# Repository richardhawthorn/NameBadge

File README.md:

### Description

NameBadge SMD

### Features

- 20 LED display
- Charlieplex LED control
- ATTINY44 processor
- 3V operation @ 1Mhz or 8Mhz
- 1x button
- ICSP port

### License

This work is licensed under a Creative Commons Attribution-ShareAlike 4.0 International License.

<br />
Designed by <a xmlns:cc="http://creativecommons.org/ns#" href="http://www.richardhawthorn.com" property="cc:attributionName" rel="cc:attributionURL" target="_blank">Richard Hawthorn</a><br />
<a rel="license" href="http://creativecommons.org/licenses/by-sa/4.0/" target="_blank">View License</a>

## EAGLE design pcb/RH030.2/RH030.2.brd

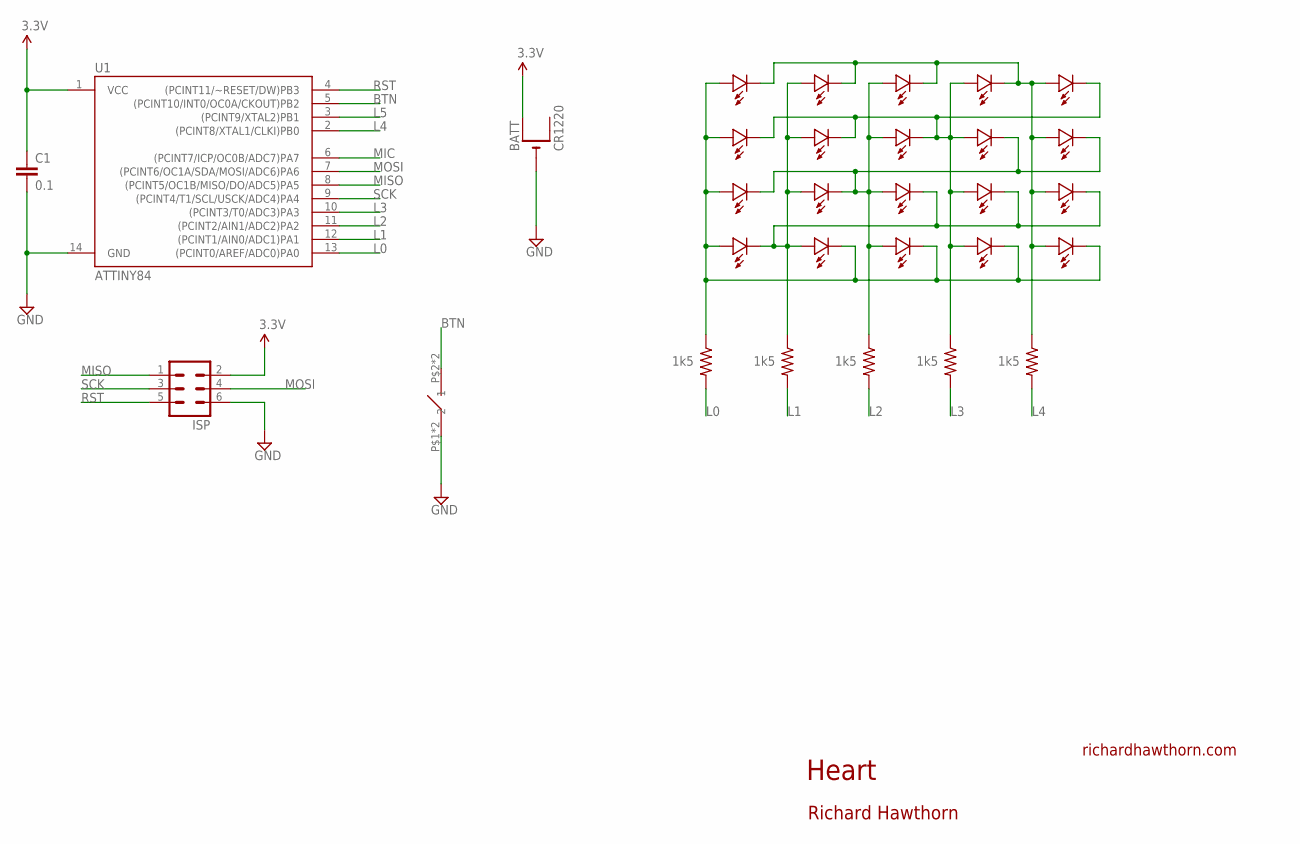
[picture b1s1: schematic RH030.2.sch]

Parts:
BATT: CR1220; CR1220-SMD
BTN1: TURTLE-3PIN
C1: 0.1; 0603-CAP
ISP: MA03-2
LED1, LED2, LED3, LED4, LED5, LED6, LED7, LED8, LED9, LED10, LED11, LED12, LED13, LED14, LED15, LED16, LED17, LED18, LED19, LED20: LED0603; 0603-LED
R1, R2, R3, R4, R5: 1k5; 0603-RES
U1: ATTINY84; SO14

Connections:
BTN: BTN1.P$2 (2), BTN1.P$4 (2), U1.5 ((PCINT10/INT0/OC0A/CKOUT)PB2)
GND: BATT.-, BTN1.P$1 (1), BTN1.P$3 (1), C1.2, ISP.6, U1.14 (GND)
L0: R1.2, U1.13 ((PCINT0/AREF/ADC0)PA0)
L1: R2.2, U1.12 ((PCINT1/AIN0/ADC1)PA1)
L2: R3.2, U1.11 ((PCINT2/AIN1/ADC2)PA2)
L3: R4.2, U1.10 ((PCINT3/T0/ADC3)PA3)
L4: R5.2, U1.2 ((PCINT8/XTAL1/CLKI)PB0)
L5: U1.3 ((PCINT9/XTAL2)PB1)
MIC: U1.6 ((PCINT7/ICP/OC0B/ADC7)PA7)
MISO: ISP.1, U1.8 ((PCINT5/OC1B/MISO/DO/ADC5)PA5)
MOSI: ISP.4, U1.7 ((PCINT6/OC1A/SDA/MOSI/ADC6)PA6)
unnamed: LED2.PLUS, LED7.PLUS, LED12.PLUS, LED13.MINUS, LED14.MINUS, LED15.MINUS, LED16.MINUS, LED17.PLUS, R2.1
unnamed: LED1.PLUS, LED6.PLUS, LED11.PLUS, LED16.PLUS, LED17.MINUS, LED18.MINUS, LED19.MINUS, LED20.MINUS, R1.1
unnamed: LED1.MINUS, LED2.MINUS, LED3.MINUS, LED4.MINUS, LED5.PLUS, LED10.PLUS, LED15.PLUS, LED20.PLUS, R5.1
unnamed: LED4.PLUS, LED5.MINUS, LED6.MINUS, LED7.MINUS, LED8.MINUS, LED9.PLUS, LED14.PLUS, LED19.PLUS, R4.1
unnamed: LED3.PLUS, LED8.PLUS, LED9.MINUS, LED10.MINUS, LED11.MINUS, LED12.MINUS, LED13.PLUS, LED18.PLUS, R3.1
RST: ISP.5, U1.4 ((PCINT11/~RESET/DW)PB3)
SCK: ISP.3, U1.9 ((PCINT4/T1/SCL/USCK/ADC4)PA4)
VCC: BATT.+$1 (+), C1.1, ISP.2, U1.1 (VCC)

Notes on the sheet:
Heart
richardhawthorn.com
Richard Hawthorn

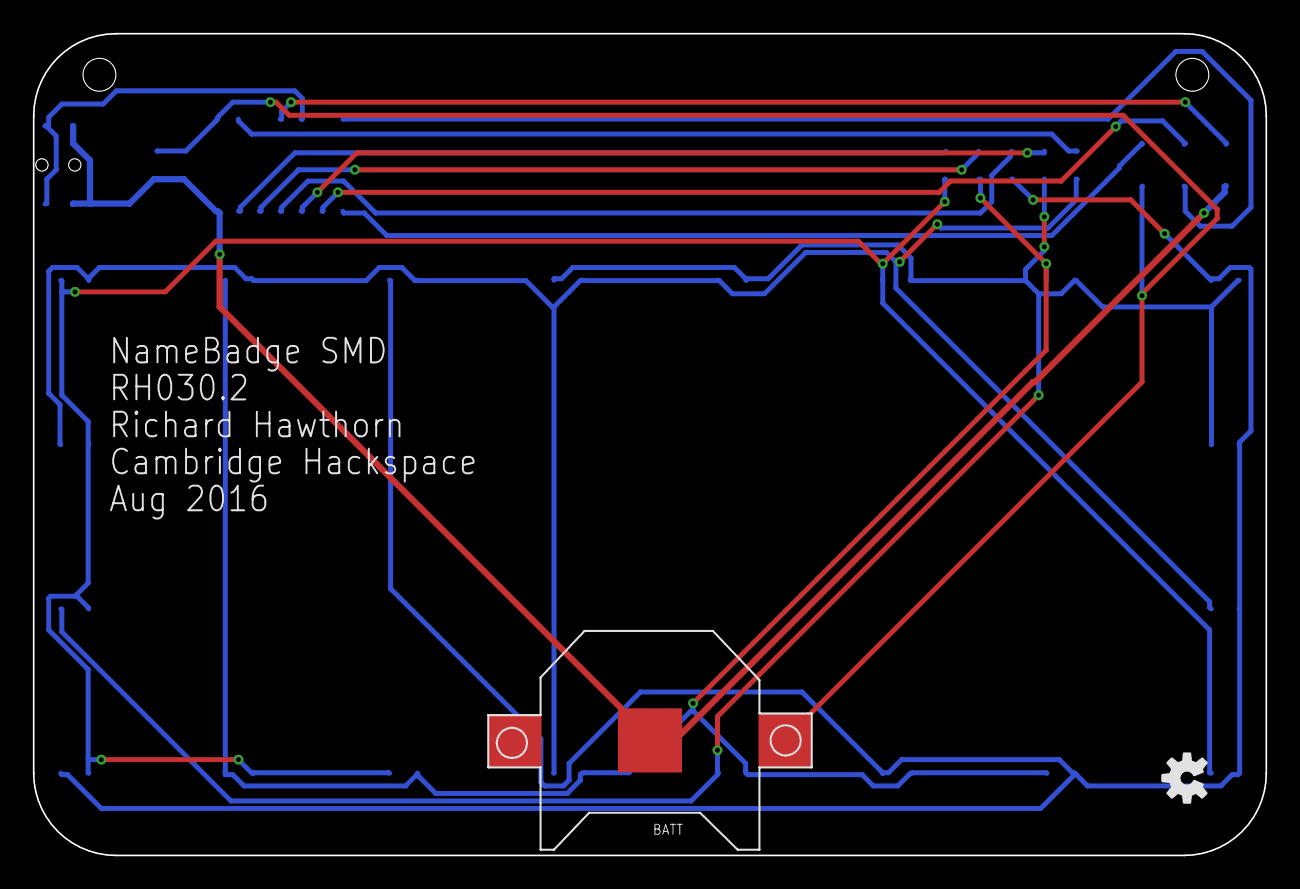
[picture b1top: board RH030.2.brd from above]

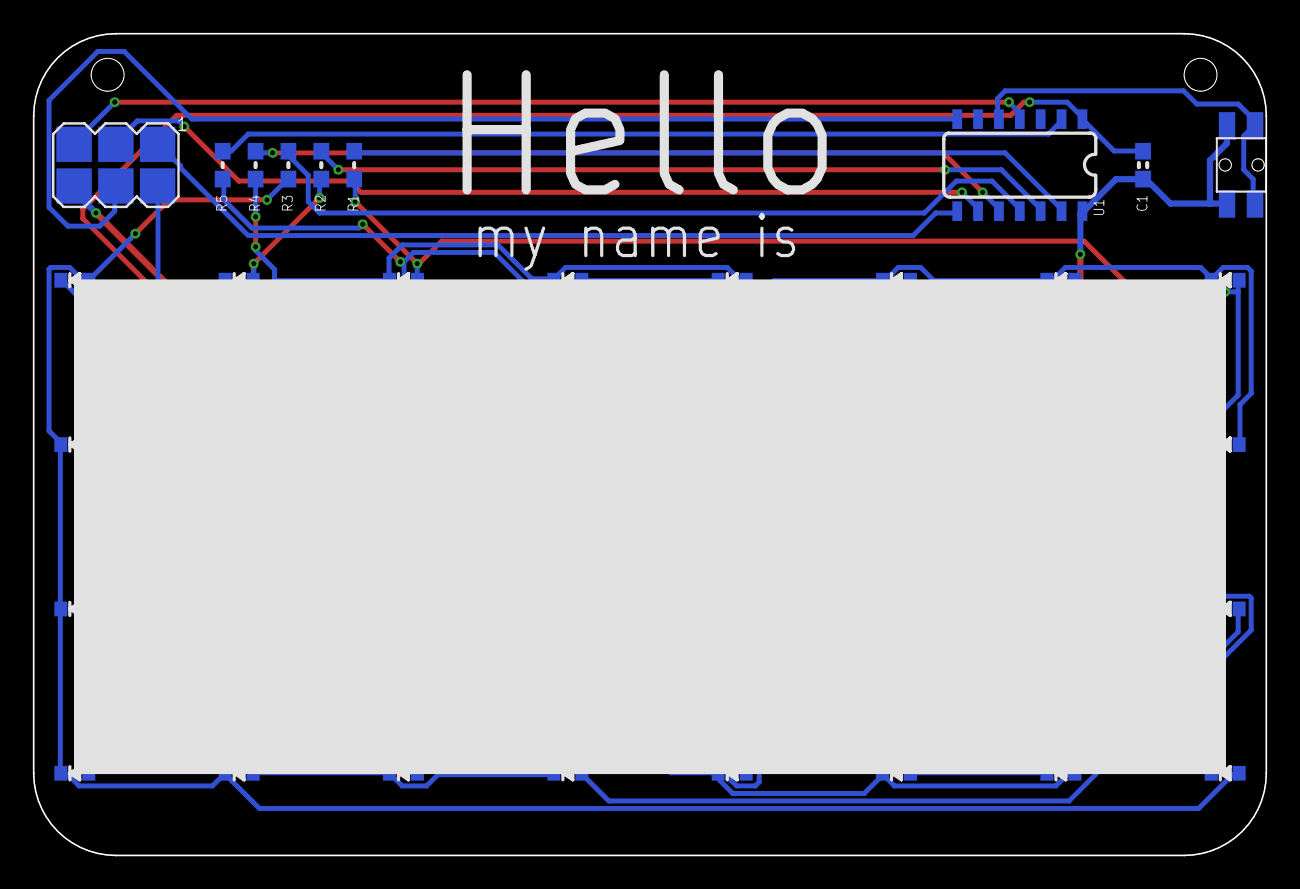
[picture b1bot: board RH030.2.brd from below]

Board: 2 copper layers, 75.0 x 50.0 mm, 31 parts (29 on the bottom side), 17 nets.

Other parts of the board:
U$3: OSHW-LOGO-S

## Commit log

2016-11-10 add pcb files

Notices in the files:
parts and their libraries:
SparkFun-Aesthetics: Licensing: CC v3.0 Share-Alike You are welcome to use this library for commercial purposes.
SparkFun-DigitalIC: Licensing: Creative Commons ShareAlike 4.0 International - https://creativecommons.org/licenses/by-sa/4.0
